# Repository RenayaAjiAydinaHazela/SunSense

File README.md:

# SunSense : Inovasi Jemuran Cerdas Otomatis untuk Rumah Tangga Modern

> *Matahari bisa absen kapan saja, tapi cucian tetap harus kering !!*
>

<aside>
⛅ Teknologi pintar yang mengikuti perubahan cuaca, menjaga jemuran Anda tetap aman di tengah kondisi tak menentu dan kesibukan yang tak bisa ditinggal

</aside>

## 💡 Tentang SunSense

**SunSense** adalah solusi inovatif untuk pengelolaan jemuran di rumah, mengintegrasikan teknologi otomatisasi dan sensor cerdas untuk menciptakan pengalaman yang lebih efisien, nyaman, dan ramah lingkungan. Dengan menggunakan mikrokontroler dan berbagai sensor, sistem ini dapat secara otomatis mengatur posisi jemuran berdasarkan kondisi cuaca terkini, memberikan kenyamanan ekstra bagi penggunanya.

Saat cuaca cerah dan kering, jemuran akan terbuka secara otomatis untuk mengeringkan pakaian. Sebaliknya, jika cuaca berubah menjadi mendung atau hujan, sistem akan menutup jemuran untuk melindungi pakaian dari hujan. Keunggulan dari **SunSense** adalah fleksibilitas yang diberikan kepada penggunanya; selain otomatis, sistem ini juga bisa dikendalikan secara manual melalui aplikasi atau tombol fisik, sehingga sesuai dengan preferensi pengguna.

Sebagai proyek open-source, **SunSense** terbuka untuk pengembangan lebih lanjut. Dengan pendekatan ini, sistem dapat beradaptasi dengan kebutuhan yang lebih beragam di masa depan, memberi peluang bagi para pengembang untuk berkontribusi dan memperkaya fungsionalitas sistem.

---

## 🎯 Visi dan Misi SunSense

### Visi

Menjadi solusi utama dalam kehidupan rumah tangga modern dengan menghadirkan sistem otomatisasi cerdas yang sederhana, hemat energi, dan mudah diakses oleh semua kalangan, sambil berfokus pada keberlanjutan dan inovasi teknologi.

### Misi

- **Inovasi Berkelanjutan:** Menghadirkan teknologi terbaru yang meningkatkan efisiensi, kenyamanan, dan kualitas hidup sehari-hari melalui otomatisasi rumah tangga.
- **Ramah Lingkungan:** Menyediakan solusi hemat energi yang dapat disesuaikan dengan penggunaan energi terbarukan, membantu rumah tangga mengurangi pemborosan energi.
- **Kolaborasi dengan Komunitas:** Mengembangkan SunSense sebagai proyek open-source yang dapat terus berkembang, dengan melibatkan komunitas untuk menciptakan solusi yang lebih baik dan lebih adaptif.
- **Menyederhanakan Kehidupan Rumah Tangga:** Memberikan kenyamanan lebih dengan otomatisasi jemuran yang merespons perubahan cuaca, sehingga pengguna dapat lebih fokus pada kegiatan mereka tanpa khawatir tentang cuaca yang berubah.
- **Mendorong Pengembangan Teknologi Cerdas:** Memperkenalkan dan memudahkan penerapan teknologi cerdas dalam kehidupan rumah tangga, mengubah rumah biasa menjadi rumah pintar yang lebih efisien dan fungsional.

Dengan pendekatan ini, **visi** dan **misi** SunSense menggabungkan konsep inovasi, ramah lingkungan, otomatisasi, dan kolaborasi komunitas, serta menyoroti pentingnya keberlanjutan dan penggunaan teknologi cerdas untuk meningkatkan kualitas hidup rumah tangga.

---

## 📌 Keunggulan SunSense

**SunSense** bukan hanya sekadar alat otomatis, tetapi sebuah solusi inovatif yang menggabungkan kecanggihan teknologi dan kenyamanan pengguna. Berikut adalah keunggulan utama dari **SunSense**:

1. **Automasi Cerdas yang Responsif**
    
    SunSense dilengkapi dengan sensor canggih yang dapat mendeteksi perubahan cuaca secara real-time. Sistem otomatis akan membuka jemuran saat cuaca cerah dan menutupnya secara otomatis saat hujan atau cuaca buruk, mengurangi kerepotan dalam mengatur jemuran secara manual.
    
2. **Kontrol Manual yang Fleksibel**
    
    Meskipun sepenuhnya otomatis, SunSense tetap memberi kebebasan kepada pengguna untuk mengatur jemuran secara manual kapan saja. Fitur kontrol manual ini memberikan fleksibilitas penuh, memungkinkan pengguna menyesuaikan pengaturan sesuai dengan kebutuhan atau situasi tertentu.
    
3. **Desain Modular dan Dapat Dikembangkan**
    
    SunSense dirancang dengan sistem modular yang memungkinkan pengguna atau pengembang untuk menyesuaikan atau mengembangkan sistem sesuai kebutuhan. Desain ini membuka peluang bagi integrasi dengan perangkat rumah pintar lainnya atau bahkan untuk penggunaan komersial di masa depan.
    
4. **Hemat Energi dan Ramah Lingkungan**
    
    Dengan konsumsi daya yang rendah, SunSense dirancang untuk efisiensi energi. Sistem ini dapat beroperasi dengan sumber daya minimal dan bahkan dapat terintegrasi dengan tenaga surya, menjadikannya pilihan yang lebih ramah lingkungan dan hemat biaya bagi rumah tangga.

Keunggulan-keunggulan ini menjadikan **SunSense** tidak hanya sebagai alat otomatis biasa, tetapi juga solusi yang memberikan kenyamanan lebih, efisiensi energi, dan fleksibilitas yang dapat berkembang sesuai kebutuhan pengguna.

---

## 📈 Potensi Pasar dan Peluang Investasi

**SunSense** memiliki potensi pasar yang besar dalam sektor rumah pintar (smart home) dan teknologi ramah lingkungan. Dengan semakin meningkatnya minat terhadap solusi rumah tangga yang otomatis dan efisien, **SunSense** siap memenuhi kebutuhan masyarakat yang menginginkan cara hidup yang lebih praktis, hemat energi, dan ramah lingkungan.

### Potensi Pasar:

1. **Rumah Tangga di Daerah Tropis atau Beriklim Tidak Menentu**
    
    Di wilayah yang sering mengalami cuaca tak menentu, seperti daerah tropis, **SunSense** akan sangat membantu dalam mengelola jemuran dengan efisien, menghindari kerugian akibat hujan mendadak, dan memastikan pakaian tetap kering tanpa harus tergantung pada cuaca.
    
2. **Layanan Laundry**
    
    Bisnis laundry dapat mengoptimalkan operasional mereka dengan menggunakan **SunSense**. Sistem otomatisasi ini memungkinkan pengelolaan jemuran yang lebih efisien, terutama untuk menanggulangi cuaca buruk, menghemat waktu, dan menjaga kualitas pakaian.
    
3. **Pengguna Rumah Pintar (Smart Homes)**
    
    **SunSense** sangat cocok untuk melengkapi ekosistem rumah pintar. Dengan teknologi otomatisasi yang dapat terintegrasi dengan perangkat rumah pintar lainnya, produk ini menawarkan kemudahan bagi pengguna yang ingin meningkatkan fungsionalitas dan efisiensi energi rumah mereka.
    
4. **Teknologi Hijau dan Energi Terbarukan**
    
    Dengan semakin tingginya kesadaran akan keberlanjutan, **SunSense** dapat menarik minat pasar yang peduli dengan solusi ramah lingkungan. Sistem yang hemat energi dan kompatibel dengan tenaga surya memberikan peluang untuk memperkenalkan teknologi hijau yang mengurangi pemborosan energi.

### Peluang Investasi:

**SunSense** bukan hanya solusi lokal, tetapi memiliki potensi besar untuk berkembang di pasar global. Seiring dengan tren meningkatnya adopsi rumah pintar dan teknologi ramah lingkungan, **SunSense** dapat meraih pangsa pasar yang lebih luas. Peluang investasi di sektor ini juga sangat menarik, karena adanya permintaan yang terus berkembang terhadap solusi yang mengintegrasikan teknologi pintar dengan kehidupan sehari-hari dan mendukung keberlanjutan.

Dengan pendekatan ini, **SunSense** tidak hanya menghadirkan inovasi yang berguna dalam kehidupan sehari-hari, tetapi juga membuka peluang besar untuk berkembang di pasar lokal dan internasional, sambil mendukung tren global menuju rumah pintar dan keberlanjutan energi.

---

## 🎓 In Collaboration With

**Dosen Pengampu :** 
Akhmad Hendriawan S.T., M.T.
197501272002121003

**Mata Kuliah :** 
Mikrokontroller

**Program Studi :** 
D4 Teknik Elektronika 

**Insititusi :** 
Politeknik Elektronika Negeri Surabaya

## 👥 Project Teams

| **NRP** | **Nama** | **Jobdesk** | **Akun** |
| --- | --- | --- | --- |
| 2123600036 | Diqta Putra Aditya |  |  |
| 2123600039 | Jonatan Arya Yoga Pratama |  |  |
| 2123600053 | Naufal Arif Zain |  |  |
| 2123600055 | Renaya Aji Aydina Hazela |  |  |
| 2123600060 | Rahma Aulia Hafidz |  |  |

---

## ✨ Mendukung Pengembangan Bersama

Sebagai proyek open-source, **SunSense** tidak hanya memberikan solusi inovatif bagi pengelolaan jemuran, tetapi juga menawarkan kesempatan bagi para pengembang, inovator, dan komunitas untuk berkolaborasi dalam menciptakan teknologi yang lebih canggih dan terintegrasi. Kolaborasi adalah kunci untuk menghasilkan solusi yang lebih baik, efisien, dan dapat diakses oleh lebih banyak orang.

Dengan mengadopsi prinsip open-source, kami mengundang Anda untuk menjadi bagian dari perjalanan ini, berkontribusi dalam pengembangan **SunSense**, dan membantu mempercepat penerapannya di berbagai sektor kehidupan, mulai dari rumah tangga hingga industri yang membutuhkan solusi efisien dan ramah lingkungan. Semua kontribusi, baik berupa kode, ide, ataupun investasi, akan memperkuat misi kami untuk menciptakan rumah tangga yang lebih efisien dan ramah lingkungan.

### Open-Source dan Kolaborasi Pengembangan

Kami percaya bahwa inovasi terbaik lahir dari kolaborasi. Oleh karena itu, **SunSense** dikembangkan dengan prinsip open-source, memberikan kesempatan kepada pengembang, akademisi, dan para hobiis untuk berkontribusi dalam memperkaya fungsionalitas dan penerapan sistem ini. Dengan pendekatan ini, kami membuka peluang bagi berbagai pihak untuk:

1. **Meningkatkan Fitur**
    
    Pengembang dapat menambahkan fitur baru seperti integrasi dengan perangkat IoT lainnya, atau pengembangan fungsionalitas tambahan yang mendukung kebutuhan rumah tangga modern.
    
2. **Memodifikasi Sistem**
    
    **SunSense** dirancang agar dapat disesuaikan dengan kebutuhan lokal maupun perkembangan teknologi baru. Kontribusi dalam modifikasi sistem akan memungkinkan adaptasi yang lebih luas dan lebih relevan di berbagai lingkungan.
    
3. **Mendorong Inovasi**
    
    Melalui kolaborasi dengan berbagai pihak, baik itu profesional, akademisi, maupun pengembang independen, kami dapat mempercepat proses inovasi dan penerapan teknologi yang ramah lingkungan dan efisien.

Kami mengundang para profesional, pengembang, dan inovator untuk bergabung dalam ekosistem **SunSense**. Bersama-sama, kita dapat menciptakan masa depan rumah tangga yang lebih cerdas, efisien, dan ramah lingkungan.

Dengan pendekatan ini, **SunSense** tidak hanya berfungsi sebagai solusi otomatisasi jemuran, tetapi juga sebagai platform terbuka untuk pengembangan bersama, membuka peluang bagi kolaborasi yang lebih luas dalam menghadirkan teknologi yang lebih baik dan lebih bermanfaat bagi masyarakat.

---

## 📞 Bergabunglah dengan Kami

**SunSense** lebih dari sekadar proyek teknologi, tetapi juga peluang untuk berinvestasi dalam menciptakan masa depan rumah tangga yang lebih cerdas, efisien, dan ramah lingkungan. Kami percaya bahwa kolaborasi adalah kunci untuk membawa inovasi ini ke lebih banyak rumah di seluruh dunia.

Jika Anda tertarik untuk berinvestasi, menjadi mitra, atau sekadar ingin mengetahui lebih banyak tentang **SunSense**, jangan ragu untuk menghubungi kami. Bersama-sama, kita dapat menghadirkan solusi rumah tangga yang lebih praktis dan terhubung dengan teknologi canggih, mendukung keberlanjutan dan efisiensi energi.

Mari wujudkan masa depan rumah tangga yang lebih pintar dan ramah lingkungan dengan bergabung bersama kami. Hubungi kami untuk lebih lanjut dan ambil bagian dalam revolusi rumah tangga pintar.

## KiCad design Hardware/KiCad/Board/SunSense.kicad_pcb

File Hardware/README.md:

# 🌞 Hardware SunSense

SunSense dikembangkan sebagai sistem pintar yang mampu merespons kondisi lingkungan secara real-time melalui sensor cahaya, hujan, suhu, dan kelembapan. Dengan memanfaatkan Arduino Nano sebagai otak utama dan modul komunikasi Bluetooth HC-05, proyek ini dirancang untuk memberikan solusi otomatisasi jemuran berbasis cuaca yang praktis dan efisien. 

Sistem ini tidak hanya dapat memantau, tetapi juga melakukan aksi langsung melalui motor servo yang dikendalikan otomatis sesuai data sensor. Pendekatan desain yang kompak, modular, dan berbasis user-experience menjadikan SunSense ideal untuk diterapkan dalam rumah tangga cerdas maupun pengembangan teknologi IoT skala kecil.

---

## ⚙️ Spesifikasi Hardware

| **Komponen** | **Tipe** | **Fungsi** |
| --- | --- | --- |
| **Mikrokontroler** | Arduino Nano | Mikrokontroler utama yang mengelola seluruh proses logika, pengambilan keputusan berdasarkan input sensor. |
| **Sensor Cahaya** | LDR | Mendeteksi intensitas pencahayaan matahari. Digunakan untuk memutuskan kapan jemuran boleh terbuka. |
| **Sensor Hujan** | FC-37 (Rain Drop) | Menentukan keberadaan air/hujan melalui hambatan listrik. Jika mendeteksi hujan (basah), sistem menutup jemuran. |
| **Sensor Suhu**  | DHT22 | Memberikan data suhu dan kelembapan lingkungan sebagai informasi tambahan untuk mengatur kondisi optimal pengeringan. |
| **Motor Servo** | SG90 | Aktuator untuk menggerakkan mekanisme buka-tutup jemuran secara otomatis. |
| **Driver Motor** | L298N | Mengatur suplai daya dan sinyal kontrol ke motor dari mikrokontroler. |
| **Regulator Tegangan** | L7805 | Mengatur dan menstabilkan tegangan 5V dari sumber daya eksternal ke komponen seperti mikrokontroler dan sensor. |
| **Bluetooth Module** | HC-05 | Komunikasi serial jarak dekat untuk kontrol manual dan monitoring via aplikasi mobile. |
| **Power Supply (Baterai)** | Ultrafire 18650A 3000mAh | Menyediakan daya untuk menggerakkan motor dan sistem kontrol secara keseluruhan. |
| **PCB** | Single Layer | Menyusun dan menyambungkan seluruh rangkaian elektronik secara rapi dan terorganisir. |
| **Bearing / Pulley** | - | Mendukung gerakan mekanik agar lebih halus, stabil, dan minim gesekan. |

---

## 📌 Diagram Pin Arduino

| Perangkat | Pin Arduino Nano | Jenis Pin | Keterangan |
| --- | --- | --- | --- |
| LDR | A1 | Analog | Sensor cahaya |
| FC-37 (Sensor Hujan) | D8 | Digital | Sensor hujan |
| DHT22 | D6 | Digital | Suhu & kelembapan |
| Servo Motor | D7 | PWM | Kendali aktuator |
| HC-05 Bluetooth | D0 (TX), D1 (RX) | UART | Komunikasi Serial |

---

## 🔌 Deskripsi Pin dan Fungsi

### 🟢 GPIO Output

### 🧭 Servo Motor

Motor servo dikendalikan melalui **pin D5** menggunakan sinyal **PWM (Pulse Width Modulation)** dari Arduino. Pergerakan servo digunakan untuk **mengoperasikan mekanisme buka-tutup jemuran** secara presisi dan otomatis. Keputusan penggerakan servo didasarkan pada hasil analisis data dari sensor lingkungan, seperti hujan, suhu, dan intensitas cahaya, guna memastikan jemuran hanya terbuka pada kondisi cuaca yang aman dan optimal.

---

### 🔁 UART Communication

### 📶 HC-05 (Bluetooth Module)

Modul HC-05 dihubungkan ke pin **D0 (TX)** dan **D1 (RX)** Arduino, memungkinkan komunikasi **serial dua arah** antara sistem dan aplikasi pada perangkat seluler. Modul ini berfungsi sebagai antarmuka **nirkabel** yang memudahkan pengguna untuk **memantau status sensor secara real-time** serta **mengontrol sistem jemuran otomatis** langsung dari jarak dekat melalui koneksi Bluetooth. Integrasi ini meningkatkan fleksibilitas dan kemudahan dalam pengoperasian sistem.

---

### 📥 Analog Input

### 🟡 LDR (Light Dependent Resistor)

Sensor LDR terhubung ke pin **A1** dan menghasilkan sinyal **analog** yang merepresentasikan intensitas pencahayaan lingkungan. Arduino membaca perubahan tegangan dalam rentang **0–5V** dan menginterpretasikannya sebagai indikator cuaca cerah atau mendung. Nilai ini digunakan sistem untuk membantu menentukan apakah jemuran otomatis perlu **dibuka atau ditutup**, berdasarkan ambang batas pencahayaan yang telah diprogram

### 📥 Digital Input

---

### 🌧️ FC-37 (Sensor Hujan)

Sensor hujan FC-37 dihubungkan ke pin **D8** dan memberikan sinyal digital berupa **HIGH** atau **LOW** berdasarkan kondisi permukaan sensornya. Ketika permukaan sensor dalam kondisi **basah**, output akan **LOW**, dan ketika **kering**, output akan **HIGH**. Informasi ini digunakan sistem sebagai indikator otomatis untuk mendeteksi keberadaan hujan dan mengaktifkan mekanisme penutupan jemuran.

### 🌡️ DHT22 (Sensor Suhu & Kelembapan)

Terhubung ke pin **D6**, sensor DHT22 menggunakan protokol komunikasi **single-wire (*One-Wire*)** untuk mengirimkan data suhu dan kelembapan secara berkala. Informasi lingkungan ini menjadi parameter pendukung yang penting dalam sistem pengambilan keputusan, guna memastikan proses pengeringan berjalan pada kondisi yang optimal dan efisien.

---

## 📦 Library Arduino

Instal melalui Library Manager di Arduino IDE:

- `DHT sensor library`
- `Adafruit Unified Sensor`
- `Servo.h` – Tersedia secara default di Arduino IDE

---

## 🏷️ Lisensi

Proyek ini merupakan inovasi berbasis mikrokontroler yang dikembangkan secara mandiri oleh mahasiswa **Electronic Engineering Polytechnic Institute of Surabaya (EEPIS)** untuk menjawab kebutuhan otomatisasi rumah tangga yang cerdas dan efisien. 
SunSense dirancang dengan pendekatan teknis yang solid, menggunakan sensor cuaca dan aktuator presisi untuk mendeteksi kondisi lingkungan secara real-time dan mengoperasikan sistem jemuran otomatis.

Proyek ini terbuka untuk dikembangkan lebih lanjut dan dapat dimodifikasi untuk kebutuhan komersial maupun edukatif, selama tetap mencantumkan sumber. Dengan pendekatan modular, efisien, dan berbasis data, SunSense menjadi solusi potensial dalam pengembangan smart home berbasis teknologi lokal yang scalable dan dapat diandalkan.

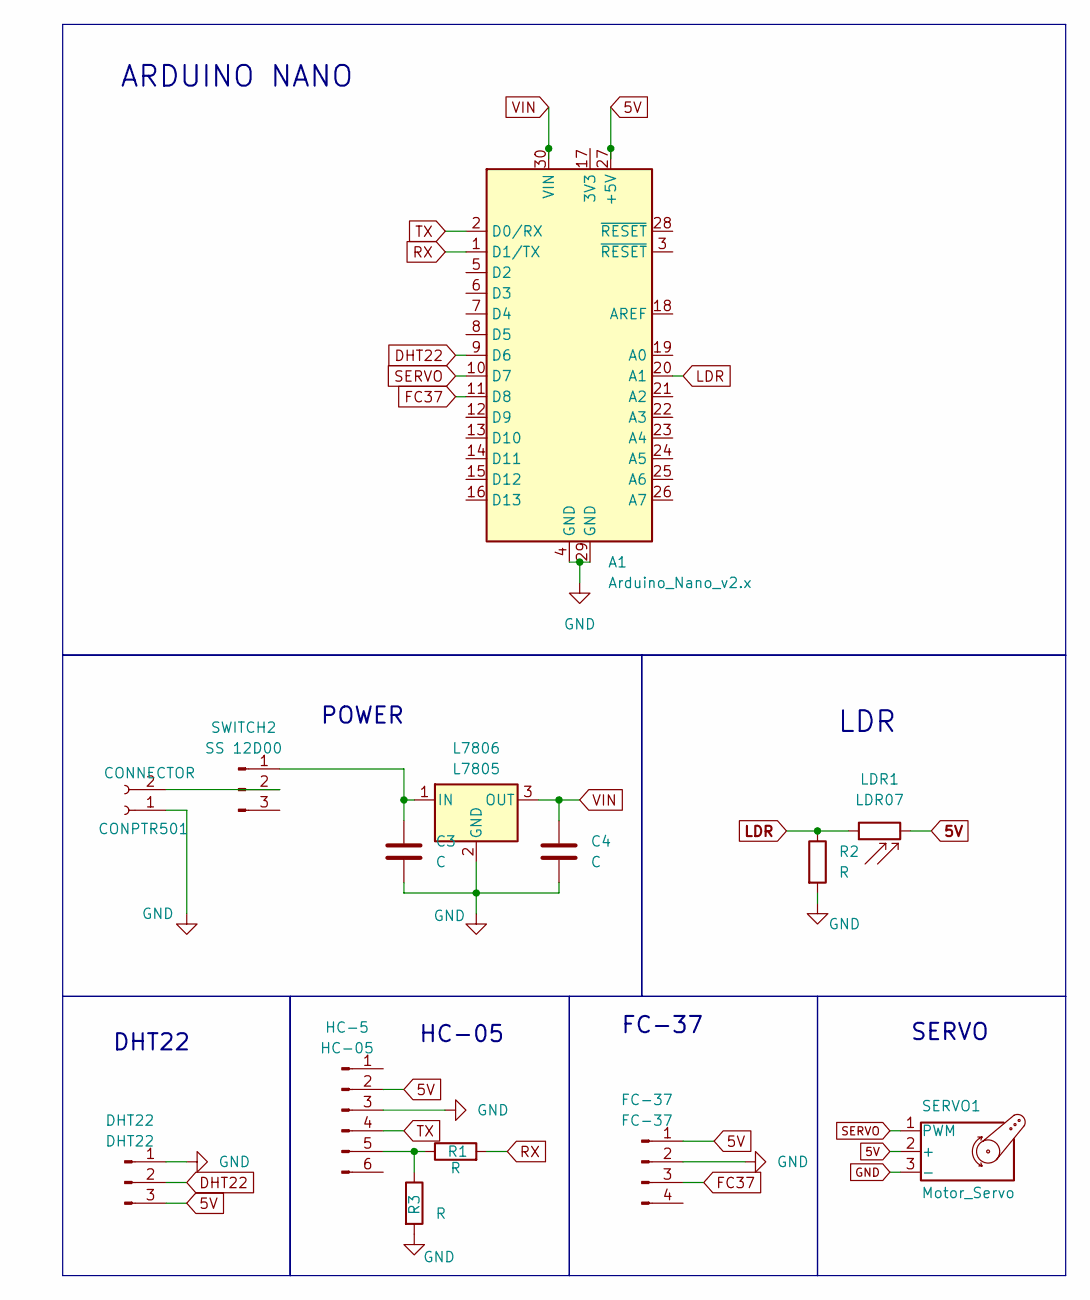
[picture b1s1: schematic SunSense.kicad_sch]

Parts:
A1: Arduino_Nano_v2.x; Arduino_Nano
C3, C4: C; C_Radial_D5.0mm_H5.0mm_P2.00mm
CONPTR501: CONNECTOR; PhoenixContact_MCV_1,5_2-G-3.81_1x02_P3.81mm_Vertical
DHT22: DHT22; PinSocket_1x03_P2.54mm_Vertical
FC-37: FC-37; PinSocket_1x04_P2.54mm_Vertical
HC-5: HC-05; PinSocket_1x06_P2.54mm_Vertical
L7806: L7805; TO-220-3_Vertical
LDR1: LDR07; R_LDR_5.1x4.3mm_P3.4mm_Vertical
R1, R2, R3: R; R_Axial_DIN0207_L6.3mm_D2.5mm_P15.24mm_Horizontal
SERVO1: Motor_Servo; PinHeader_1x03_P2.54mm_Vertical
SWITCH2: SS 12D00; SW_CK_JS202011CQN_DPDT_Straight

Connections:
5V: A1.27 (+5V), DHT22.3, FC-37.1, HC-5.2, LDR1.2, SERVO1.2 (+)
DHT22: A1.9 (D6), DHT22.2
FC37: A1.11 (D8), FC-37.3
GND: A1.4 (GND), A1.29 (GND), C3.2, C4.2, CONPTR501.1, DHT22.1, FC-37.2, HC-5.3, L7806.2 (GND), R2.2, R3.2, SERVO1.3 (-)
LDR: A1.20 (A1), LDR1.1, R2.1
unnamed: CONPTR501.2, SWITCH2.2
unnamed: HC-5.5, R1.1, R3.1
unnamed: C3.1, L7806.1 (IN), SWITCH2.1
RX: A1.1 (D1/TX), R1.2
SERVO: A1.10 (D7), SERVO1.1 (PWM)
TX: A1.2 (D0/RX), HC-5.4
VIN: A1.30 (VIN), C4.1, L7806.3 (OUT)

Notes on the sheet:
HC-05
ARDUINO NANO
LDR
FC-37
POWER
SERVO
DHT22

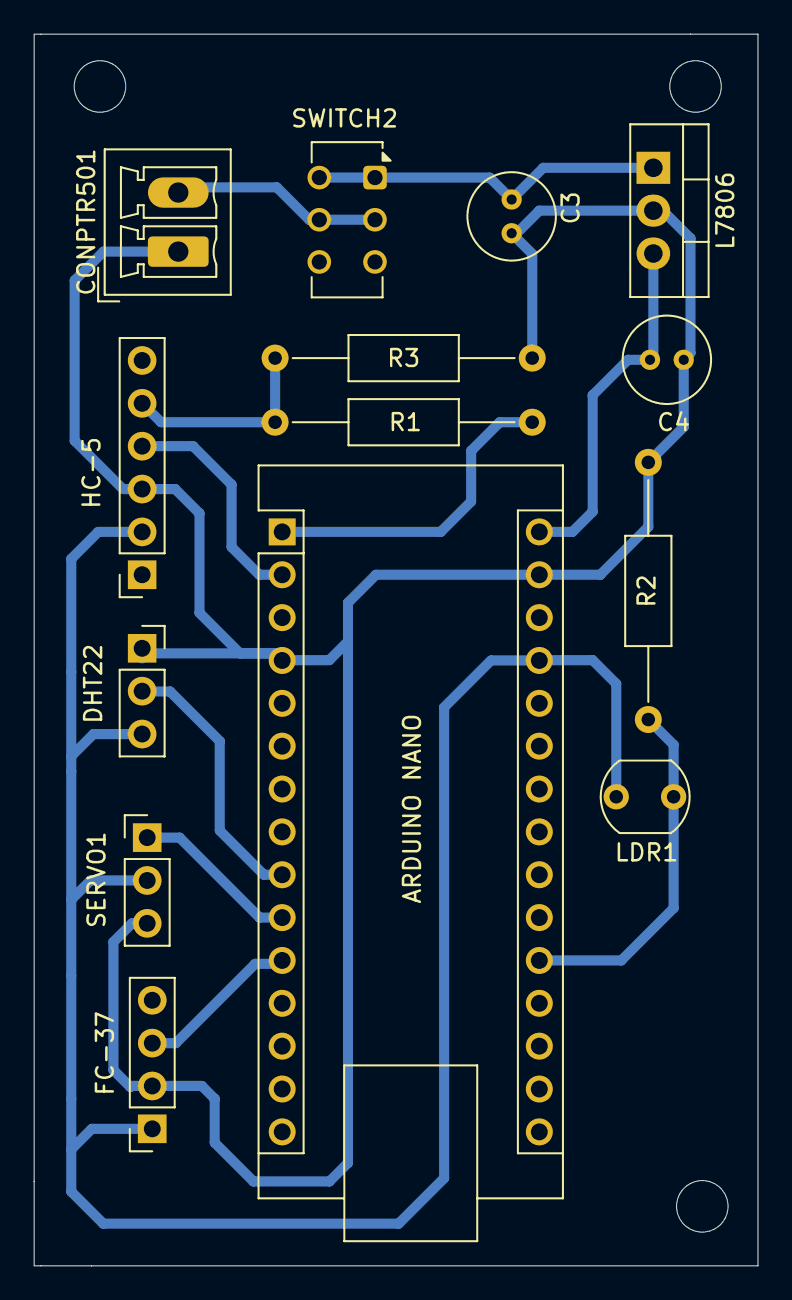
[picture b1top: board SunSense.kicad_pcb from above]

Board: 2 copper layers, 42.9 x 73.0 mm, 14 parts (0 on the bottom side), 12 nets.

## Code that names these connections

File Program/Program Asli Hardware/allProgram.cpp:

#include <Arduino.h>
#include <Servo.h>
#include <DHT.h>

// Pin Configuration
#define DHT_PIN 6
#define DHT_TYPE DHT22
#define LDR_PIN A1
#define RAIN_SENSOR_PIN 8
#define SERVO_PIN 7
#define MODE_BUTTON_PIN 3
#define CONTROL_BUTTON_PIN 2

const unsigned long DHT_READ_INTERVAL = 1000;
const int LDR_DARK = 300;
const int UPDATE_INTERVAL = 500;
const int DEBOUNCE_DELAY = 50;
const int HUMID_THRESHOLD = 70;

DHT dht(DHT_PIN, DHT_TYPE);
Servo myservo;

struct SensorData {
  float temperature = 0;
  float humidity = 0;
  int light;
  bool rain;
  bool decision;
} data;

bool manualMode = false;
bool manualDecision = false;

unsigned long lastUpdate = 0;
unsigned long lastModeButtonPress = 0;
unsigned long lastControlButtonPress = 0;

// Fungsi gerakan servo halus
void smoothServoMove(int targetAngle) {
  int currentAngle = myservo.read();
  if (currentAngle == targetAngle) return;

  int step = (currentAngle < targetAngle) ? 1 : -1;
  for (int angle = currentAngle; angle != targetAngle; angle += step) {
    myservo.write(angle);
    delay(10);  // Sesuaikan kecepatan
  }
  myservo.write(targetAngle);  // Pastikan posisi akhir tepat
}

void updateSensors() {
  static unsigned long lastDHTRead = 0;
  if (millis() - lastDHTRead >= DHT_READ_INTERVAL) {
    float t = dht.readTemperature();
    float h = dht.readHumidity();
    if (!isnan(t)) data.temperature = t;
    if (!isnan(h)) data.humidity = h;
    lastDHTRead = millis();
  }

  data.light = analogRead(LDR_PIN);
  data.rain = digitalRead(RAIN_SENSOR_PIN) == LOW;
}

void makeAutomaticDecision() {
  bool raining = data.rain;
  bool dark = data.light < LDR_DARK;
  bool cold = data.temperature < 25.0;
  bool humid = data.humidity > HUMID_THRESHOLD;
  data.decision = !(raining || (dark && cold) || (dark && humid));
}

void controlServo() {
  int targetAngle = 0;
  if (manualMode) {
    targetAngle = manualDecision ? 45 : 0;
  } else {
    targetAngle = data.decision ? 45 : 0;
  }
  smoothServoMove(targetAngle);
}

void sendData() {
  Serial.print("<MODE:");
  Serial.print(manualMode ? "MANUAL" : "AUTO");
  Serial.print("|T:");
  Serial.print(data.temperature, 1);
  Serial.print("|H:");
  Serial.print(data.humidity, 1);
  Serial.print("|L:");
  Serial.print(data.light);
  Serial.print("|R:");
  Serial.print(data.rain ? "RAINING" : "DRY");
  Serial.print("|D:");
  Serial.println((manualMode ? manualDecision : data.decision) ? "OUT" : "IN");
  Serial.println(">");
}

void readModeButton() {
  static bool lastState = HIGH;
  bool currentState = digitalRead(MODE_BUTTON_PIN);
  if (lastState == HIGH && currentState == LOW) {
    if (millis() - lastModeButtonPress > DEBOUNCE_DELAY) {
      manualMode = !manualMode;
      lastModeButtonPress = millis();
    }
  }
  lastState = currentState;
}

void readControlButton() {
  static bool lastState = HIGH;
  bool currentState = digitalRead(CONTROL_BUTTON_PIN);
  if (manualMode && lastState == HIGH && currentState == LOW) {
    if (millis() - lastControlButtonPress > DEBOUNCE_DELAY) {
      manualDecision = !manualDecision;
      lastControlButtonPress = millis();
    }
  }
  lastState = currentState;
}

void handleSerialCommand() {
  if (Serial.available()) {
    char cmd = Serial.read();
    if (cmd == 'm') {
      manualMode = !manualMode;
      Serial.println(manualMode ? "MODE:MANUAL" : "MODE:AUTO");
    } else if (cmd == 'c' && manualMode) {
      manualDecision = !manualDecision;
      Serial.println(manualDecision ? "POS:OUT" : "POS:IN");
    }
  }
}

void setup() {
  Serial.begin(9600);
  dht.begin();
  myservo.attach(SERVO_PIN);
  myservo.write(0);  // Posisi awal

  pinMode(RAIN_SENSOR_PIN, INPUT);
  pinMode(MODE_BUTTON_PIN, INPUT_PULLUP);
  pinMode(CONTROL_BUTTON_PIN, INPUT_PULLUP);
}

void loop() {
  readModeButton();
  readControlButton();
  handleSerialCommand();

  if (millis() - lastUpdate > UPDATE_INTERVAL) {
    updateSensors();
    if (!manualMode) {
      makeAutomaticDecision();
    }
    controlServo();
    sendData();
    lastUpdate = millis();
  }
}

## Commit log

2025-04-28 Nambahin Folder
2025-05-02 Update allProgram.cpp
    Update Sensor DHT22 dan LDR (Rain Sensor pake push button)
2025-05-02 Update README.md
    Membetulkan readme bagian bawah
2025-05-07 Konsep SunSense
    Memaparkan konsep SunSense yang ingin kami hadirkan sebagai salah satu solusi permasalahan yang ada
2025-05-07 Blok Diagram dan Alur Sistem
    Blok diagram dari sistem SunSense sekaligus penjelasan alur dari sistem tersebut
2025-05-07 Create Block Diagram dan Alur Sistem
2025-05-07 Pemaparan Blok Diagram dan Alur Sistem
    Menggambarkan blok diagram dari rancangan SunSense dengan penjelasan alur sistem untuk merincikan cara kerja dari sistem SunSense
2025-05-07 Alur Sistem
    Penjelasan alur sistem dari blok diagram yang ada pada SunSense
2025-05-10 Buat Folder Asset
    buat folder aset yang kedepannya akan di buat gambar simulasi , video simulasi atau demo program
2025-05-10 Delete Program/Asset/Readme.md
    hapus file dummy untuk buat folder di awal
2025-05-10 Update README.md
    Membetulkan path gambar ke file yang ada di dalam folder aset
2025-05-10 Delete Program/Screenshot 2025-04-29 114008.png
    ngehapus gambar simulasi karena gambar udah dipindah kedalam folder aset
2025-05-11 Nambah Folder program GUI
    Nambah Folder program GUI untuk Penempatan program python untuk me monitoring data dari arduino nano
2025-05-11 Delete Program/Program GUI/readme.md
    hapus file dummy untuk buat folder program gui di awal , dan sekarang sudah ada isinya yaitu sunsense.py
2025-05-11 Add KiCad schematic file for circuit design
    This commit includes the main schematic file (.kicad_sch) created in KiCad for documenting and sharing the circuit design. This schematic serves as the base for PCB layout and collaboration.
2025-05-11 Add KiCad PCB layout file (.kicad_pcb)
    Uploaded the PCB layout file generated from the schematic. This file contains the physical design of the circuit, including component placements and routing. Designed using KiCad for fabrication and 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
2025-05-11 Add 3D render image of PCB layout
    Uploaded a rendered image of the PCB in 3D view from KiCad. This visual helps with presentation, documentation, and verifying component placement and orientation.
2025-05-11 Update README.md
    Menambahkan deskripsi tentang semua yang berhubungan dengan hardware dan mikrokontroler yang digunakan.
2025-05-11 Delete Hardaware/SunSense.kicad_sch
    Karena akan diganti dengan versi .png
2025-05-11 Add KiCad Schematic file (.png)
    This commit includes the main schematic file (.kicad_sch) created in KiCad for documenting and sharing the circuit design. This schematic serves as the base for PCB layout and collaboration.
2025-05-11 Create Folder and Sub-folder
    Menambahkan folder Kicad dan sub-folder Schematic
2025-05-11 Rename folder "Hardaware" to "Hardware"
2025-05-11 Menambahkan folder dan sub-folder
    Menambahkan folder Kicad dan sub-folder Schematic
2025-05-11 Add KiCad Schematic
    Berisi file .png dan juga file .sch dari KiCad
2025-05-11 Create Folder KiCad
2025-05-11 Create Folder Schematic
2025-05-11 Add KiCad Schematic
    Berisi file .png dan juga .sch dari KiCad
2025-05-11 Create folder Board
2025-05-11 Add KiCad Board
    Berisi file .png dan juga .pcb KiCad
2025-05-11 Create a
2025-05-11 Add 3D Viewer from KiCad
    Berisi gambaran PCB bagian depan dan belakang.
2025-05-11 Update README.md
    Memperbarui preview agar path langsung menuju gambar yang tersedia.
2025-05-11 Update README.md
    Memperbarui preview (lagi)
2025-05-11 Update README.md
    Memperbarui preview.
2025-05-11 Update README.md
    Menghapus preview.
2025-05-11 Update README.md
    memperbarui deskripsi awal.
2025-05-11 Menata readme program agar lebih sedikit tulisan dan enak dibaca
2025-05-11 Update README.md
    Memperbarui komponen dan juga harganya.
2025-05-11 Update README.md
    Memperbarui tampilan "komponen" dan sedikit memperbaiki keterangan yang ada.
2025-05-11 Nambah Foto Simulasi yg lebih Fokus Ke Komponen
2025-05-11 Benerin Gambar Simul biar fokus ke komponen yg di simulasikan
2025-05-11 Update README.md (nambah pin utk inisialisasi ke program)
2025-05-11 Update allProgram.cpp (ganti pin rain sensor dan ngasih penjelasan)
2025-05-11 Nambah Foto SImul Fix
2025-05-11 Update README.md (nambah foto simul yang udah fix)
2025-05-11 GUI Python (belum fix)
2025-05-11 Update README.md (nambahin tabel untuk penjelasan komponen di simulasi)
2025-05-18 Update allProgram.cpp ganti raindrop jadi sensor beneran
2025-05-19 Pemaparan Visualisasi 3D Design
2025-05-19 penjelasan pemaparan desain UI/UX
2025-05-19 perbaikan pemaparan desain 3D
2025-05-19 perbaikan komponen
2025-05-19 perbaikan pemaparan hardware
2025-05-19 perbaikan kata
2025-05-19 perbaikan pemaran software
2025-05-19 Delete Hardware/KiCad/3D Design/3D Design from Board SunSense (behind).png
    Mengganti file dengan yang baru
2025-05-19 Add 3D Design PCB
    Berisi file .png
2025-05-19 Delete Hardware/KiCad/3D Design/3D Design from Board SunSense (front).png
    Mengganti dengan file baru
2025-05-19 Add 3D Design Preview
    Berisi file .png
2025-05-19 Delete Hardware/KiCad/Board/Board SunSunse from KiCad.png
    Mengganti dengan yang baru
2025-05-19 Add PCB Layout Preview
    Berisi file .png
2025-05-19 Delete Hardware/KiCad/Board/SunSense.kicad_pcb
    mengganti dengan file baru
2025-05-19 Add File PCB from KiCad
    Berisi file KiCad Board
2025-05-19 Delete Hardware/KiCad/Schematic/Schematic SunSense from KiCAD.png
    Mengganti dengan file baru
2025-05-19 Delete Hardware/KiCad/Schematic/SunSense.kicad_sch
    Mengganti dengan file baru
2025-05-19 Create Schematic folder
2025-05-19 Add Schematic Files
    Berisi file .png dan .kicad_sch
2025-05-19 Update README.md
    Menambahkan spesifikasi hardware
2025-05-19 Update README.md
    Memperbaiki koneksi pin
2025-05-20 Update allProgram.cpp (ganti pin)
2025-05-20 nambah program versi baremetal
